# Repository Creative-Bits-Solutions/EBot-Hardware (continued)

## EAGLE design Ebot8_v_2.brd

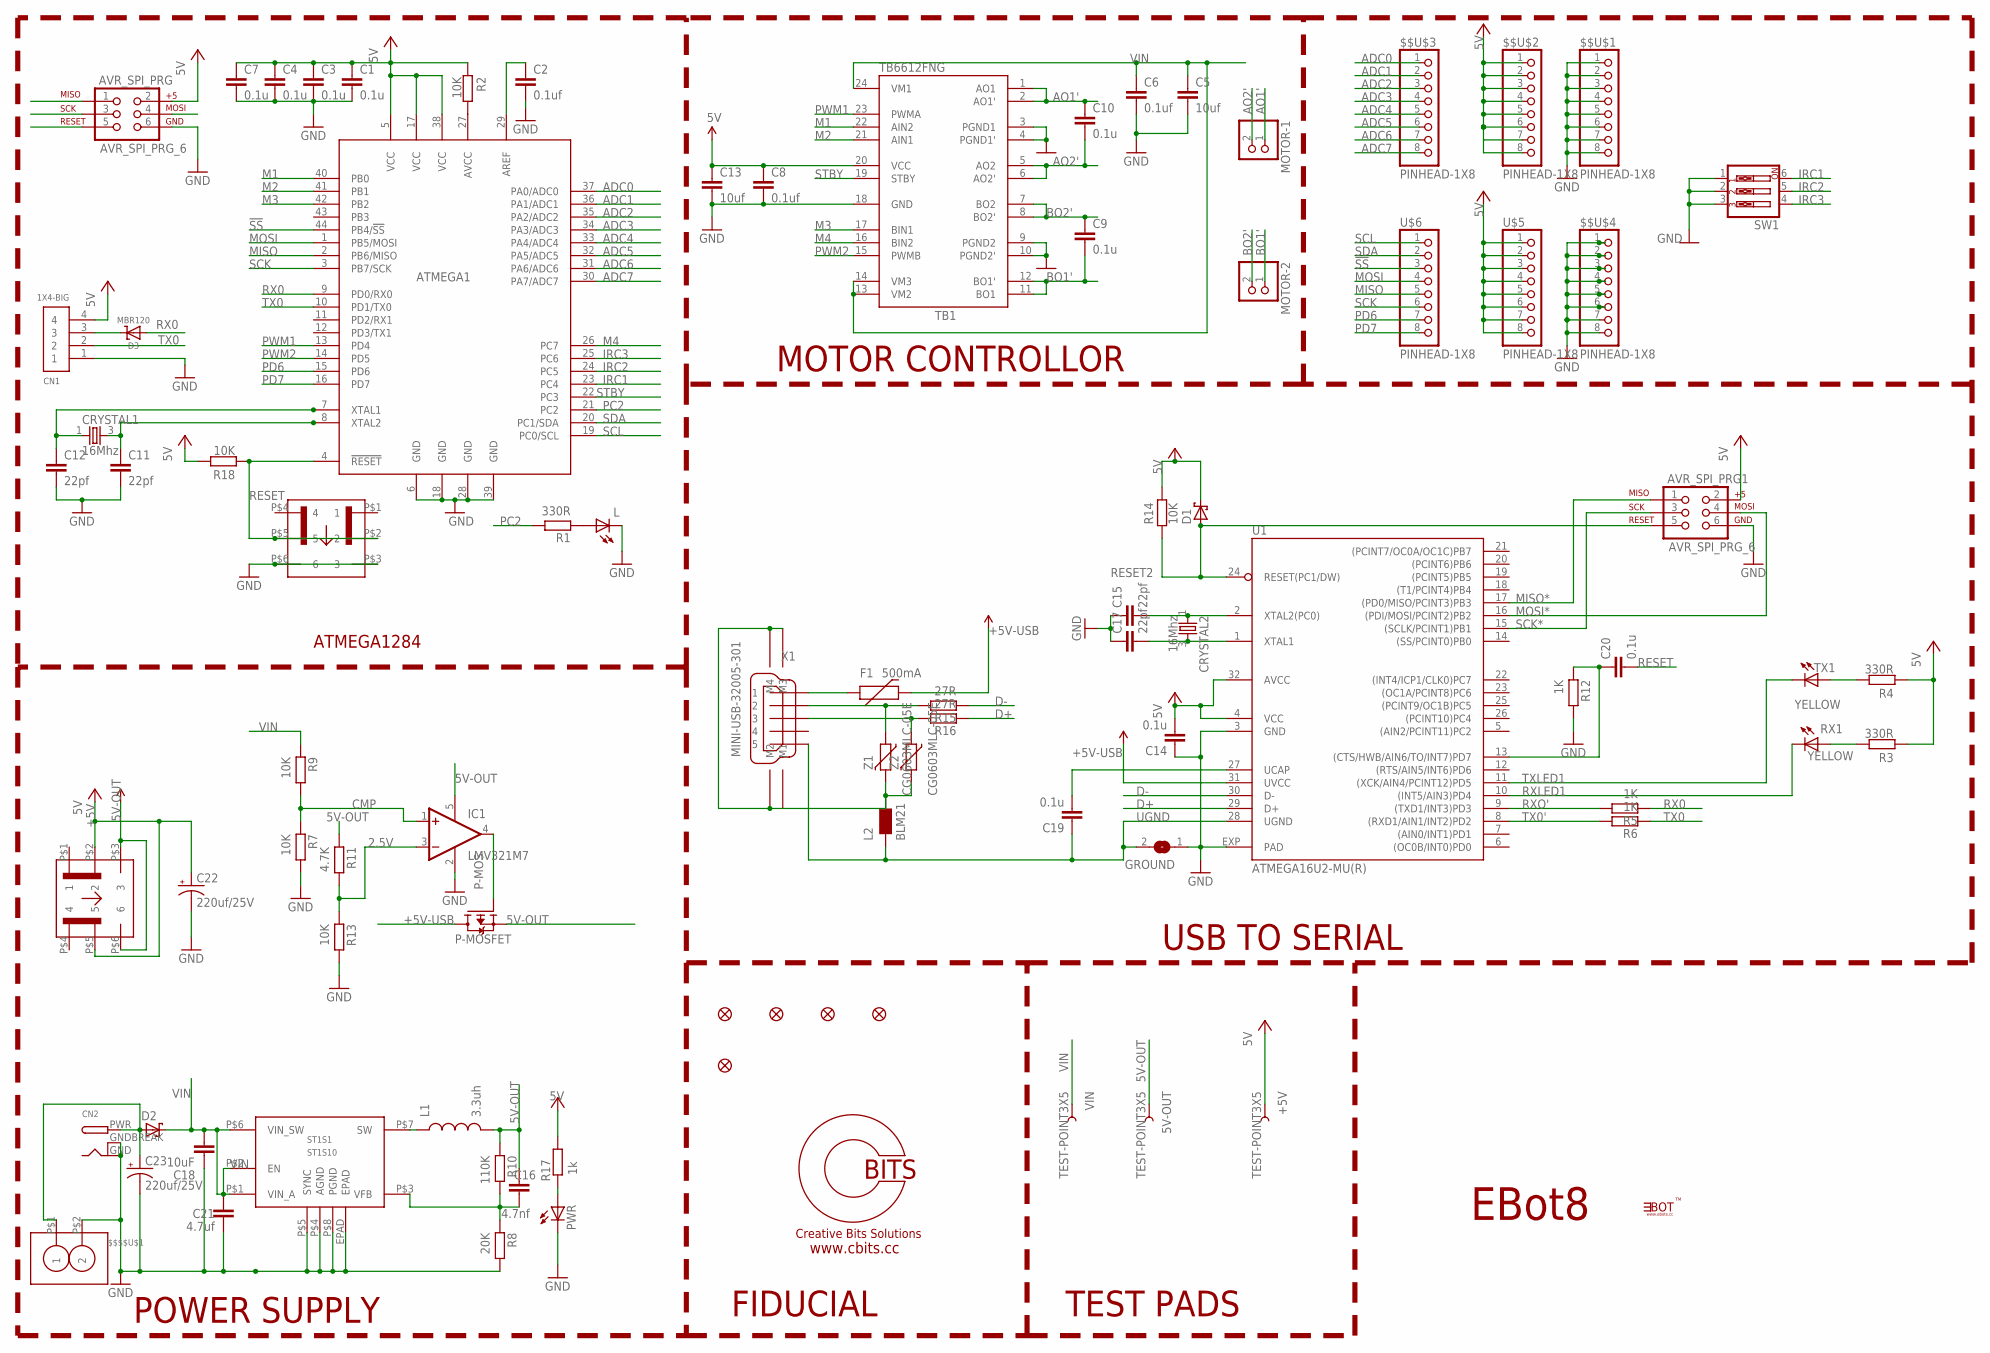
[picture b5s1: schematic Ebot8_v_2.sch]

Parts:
5V-OUT: TEST-POINT3X5; PAD.03X.05
$$$$U$1: SCREW_CONNECTOR-2PIN-; SCREW_CONNECTOR-2PIN-5.08MM
$$U$1, $$U$2, $$U$3, $$U$4: PINHEAD-1X8
+5V: TEST-POINT3X5; PAD.03X.05
ATMEGA1: ATMEGA164A/PA/324A/PA/644A/PA/1284/P; 44TQFP
AVR_SPI_PRG, AVR_SPI_PRG1: AVR_SPI_PRG_6; 2X3
C1, C3, C4, C7, C9, C10, C14, C19, C20: 0.1u; C0603
C2, C6, C8: 0.1uf; C0603
C5, C13: 10uf; C0603
C11, C12, C15, C17: 22pf; C0603
C16: 4.7nf; C0603
C18: 10uF; C0603
C21: 4.7uf; C0603
C22, C23: 220uf/25V; E2,5-6
CN1: 1X4-BIG; 1X04-BIG
CN2: DCBARRELPTH; DCJACK_2MM_PTH
CRYSTAL1, CRYSTAL2: 16Mhz; CRYSTAL-4PIN
D1, D2: SCHOTTKY-DIODESMA2; SCHOTTKY_SMA
D3: MBR120; SOD-123
F1: 500mA; PTC-1206
FID1, FID2, FID3, FID4, FID100: FIDUCIAL1.5X3; FIDUCIAL-1.5X3
GROUND: SJ
IC1: LMV321M7; SC70-5L
L: LEDCHIP-LED0603; CHIP-LED0603
L1: 3.3uh; CR54
L2: BLM21; 0805
LOGO1: CBITS_LOGO
MOTOR-1, MOTOR-2: PINHD-1X2; 1X02
P-MOS: P-MOSFET; SOT23-R
POWER: PUSHBUTTON_SWITCH-CW179-ND; PUSHBUTTON_SWITCH
PWR: LEDCHIP-LED0603; CHIP-LED0603
R1, R3, R4: 330R; R0603
R2, R7, R9, R13, R14, R18: 10K; R0603
R5, R6, R12: 1K; R0603
R8: 20K; R0603
R10: 110K; R0603
R11: 4.7K; R0603
R15, R16: 27R; R0603
R17: 1k; R0603
RESET: PUSHBUTTON_SWITCH-ON-MOM; PUSHBUTTON_SWITCH
RX1: YELLOW; CHIP-LED0603
ST1S1: ST1S10
SW1: SW_DIP-3; EDG-03
TB1: TB6612FNG; SSOP24
TX1: YELLOW; CHIP-LED0603
U1: ATMEGA16U2-MU(R); SMARTPRJ_ATMEL_QFN32
U$5, U$6: PINHEAD-1X8
U$14: EBOT_LOGO
VIN: TEST-POINT3X5; PAD.03X.05
X1: MINI-USB-32005-301; 32005-301
Z1, Z2: CG0603MLC-05E; CT/CN0603

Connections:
2.5V: IC1.3 (-IN), R11.2, R13.1
5V-OUT: 5V-OUT.P$1, C16.1, IC1.5 (V+), L1.P$2 (2), P-MOS.2 (S), POWER.P$3 (3), POWER.P$6 (6), R10.1, R11.1
!SS: ATMEGA1.44 (PB4/!SS), U$6.3
+5V: $$U$2.1, $$U$2.2, $$U$2.3, $$U$2.4, $$U$2.5, $$U$2.6, $$U$2.7, $$U$2.8, +5V.P$1, ATMEGA1.5 (VCC), ATMEGA1.17 (VCC), ATMEGA1.38 (VCC), AVR_SPI_PRG.2, AVR_SPI_PRG1.2, C1.1, C3.1, C4.1, C7.1, C8.1, C13.1, C14.2, C22.+, CN1.4, D1.C, POWER.P$2 (2), POWER.P$5 (5), R2.1, R3.1, R4.1, R14.2, R17.2, R18.2, TB1.20 (VCC), U1.4 (VCC), U1.32 (AVCC), U$5.1, U$5.2, U$5.3, U$5.4, U$5.5, U$5.6, U$5.7, U$5.8
+5V-USB: F1.2, P-MOS.3 (D), U1.31 (UVCC)
ADC0: $$U$3.1, ATMEGA1.37 (PA0/ADC0)
ADC1: $$U$3.2, ATMEGA1.36 (PA1/ADC1)
ADC2: $$U$3.3, ATMEGA1.35 (PA2/ADC2)
ADC3: $$U$3.4, ATMEGA1.34 (PA3/ADC3)
ADC4: $$U$3.5, ATMEGA1.33 (PA4/ADC4)
ADC5: $$U$3.6, ATMEGA1.32 (PA5/ADC5)
ADC6: $$U$3.7, ATMEGA1.31 (PA6/ADC6)
ADC7: $$U$3.8, ATMEGA1.30 (PA7/ADC7)
AO1': C10.1, MOTOR-1.1, TB1.1 (AO1), TB1.2 (AO1')
AO2': C10.2, MOTOR-1.2, TB1.5 (AO2), TB1.6 (AO2')
AREF: ATMEGA1.29 (AREF), C2.1
BO1': C9.2, MOTOR-2.1, TB1.11 (BO1), TB1.12 (BO1')
BO2': C9.1, MOTOR-2.2, TB1.7 (BO2), TB1.8 (BO2')
CMP: IC1.1 (+IN), R7.1, R9.2
D+: R16.1, U1.29 (D+)
D-: R15.1, U1.30 (D-)
GATE_CMD: IC1.4 (OUT), P-MOS.1 (G)
GND: $$$$U$1.P$2 (2), $$U$1.1, $$U$1.2, $$U$1.3, $$U$1.4, $$U$1.5, $$U$1.6, $$U$1.7, $$U$1.8, $$U$4.1, $$U$4.2, $$U$4.3, $$U$4.4, $$U$4.5, $$U$4.6, $$U$4.7, $$U$4.8, ATMEGA1.6 (GND), ATMEGA1.18 (GND), ATMEGA1.28 (GND), ATMEGA1.39 (GND), AVR_SPI_PRG.6, AVR_SPI_PRG1.6, C1.2, C2.2, C3.2, C4.2, C5.2, C6.2, C7.2, C8.2, C11.2, C12.2, C13.2, C14.1, C15.1, C17.1, C18.2, C21.2, C22.-, C23.-, CN1.1, CN2.GND, CN2.GNDBREAK, GROUND.1, IC1.2 (V-), L.C, PWR.C, R7.2, R8.2, R12.2, R13.2, RESET.P$3 (3), RESET.P$6 (6), ST1S1.EPAD, ST1S1.P$4 (AGND), ST1S1.P$5 (SYNC), ST1S1.P$8 (PGND), ST1S1.P$9 (GND), ST1S1.P$10 (GND), ST1S1.P$11 (GND), ST1S1.P$12 (GND), ST1S1.P$13 (GND), ST1S1.P$14 (GND), ST1S1.P$15 (GND), ST1S1.P$16 (GND), ST1S1.P$17 (GND), SW1.1, SW1.2, SW1.3, TB1.3 (PGND1), TB1.4 (PGND1'), TB1.9 (PGND2), TB1.10 (PGND2'), TB1.18 (GND), U1.3 (GND), U1.EXP (PAD)
IRC1: ATMEGA1.23 (PC4), SW1.6
IRC2: ATMEGA1.24 (PC5), SW1.5
IRC3: ATMEGA1.25 (PC6), SW1.4
M1: ATMEGA1.40 (PB0), TB1.22 (AIN2)
M2: ATMEGA1.41 (PB1), TB1.21 (AIN1)
M3: ATMEGA1.42 (PB2), TB1.17 (BIN1)
M4: ATMEGA1.26 (PC7), TB1.16 (BIN2)
MISO: ATMEGA1.2 (PB6/MISO), AVR_SPI_PRG.1, U$6.5
MISO*: AVR_SPI_PRG1.1, U1.17 ((PD0/MISO/PCINT3)PB3)
MOSI: ATMEGA1.1 (PB5/MOSI), AVR_SPI_PRG.4, U$6.4
MOSI*: AVR_SPI_PRG1.4, U1.16 ((PDI/MOSI/PCINT2)PB2)
unnamed: PWR.A, R17.1
unnamed: $$$$U$1.P$1 (1), C23.+, CN2.PWR, D2.A
unnamed: R3.2, RX1.A
unnamed: R4.2, TX1.A
unnamed: C15.2, CRYSTAL2.1, U1.2 (XTAL2(PC0))
unnamed: ATMEGA1.27 (AVCC), R2.2
unnamed: C17.2, CRYSTAL2.3 (2), U1.1 (XTAL1)
unnamed: C19.2, U1.27 (UCAP)
unnamed: C20.1, R12.1, U1.13 ((CTS/HWB/AIN6/TO/INT7)PD7)
unnamed: L2.2, X1.M1, X1.M2, X1.M3, X1.M4, Z1.2, Z2.2
unnamed: CN1.3, D3.C
unnamed: L.A, R1.1
unnamed: F1.1, X1.1
unnamed: R15.2, X1.2, Z1.1
unnamed: R16.2, X1.3, Z2.1
unnamed: L1.P$1 (1), ST1S1.P$7 (SW)
unnamed: C16.2, R8.1, R10.2, ST1S1.P$3 (VFB)
unnamed: ATMEGA1.8 (XTAL2), C11.1, CRYSTAL1.3 (2)
unnamed: ATMEGA1.7 (XTAL1), C12.1, CRYSTAL1.1
PC2: ATMEGA1.21 (PC2), R1.2
PD6: ATMEGA1.15 (PD6), U$6.7
PD7: ATMEGA1.16 (PD7), U$6.8
PWM1: ATMEGA1.13 (PD4), TB1.23 (PWMA)
PWM2: ATMEGA1.14 (PD5), TB1.15 (PWMB)
RESET: ATMEGA1.4 (!RESET), AVR_SPI_PRG.5, C20.2, R18.1, RESET.P$2 (2), RESET.P$5 (5)
RESET2: AVR_SPI_PRG1.5, D1.A, R14.1, U1.24 (RESET(PC1/DW))
RX0: ATMEGA1.9 (PD0/RX0), D3.A, R5.1
RXLED1: RX1.C, U1.10 ((INT5/AIN3)PD4)
RXO': R5.2, U1.9 ((TXD1/INT3)PD3)
SCK: ATMEGA1.3 (PB7/SCK), AVR_SPI_PRG.3, U$6.6
SCK*: AVR_SPI_PRG1.3, U1.15 ((SCLK/PCINT1)PB1)
SCL: ATMEGA1.19 (PC0/SCL), U$6.1
SDA: ATMEGA1.20 (PC1/SDA), U$6.2
STBY: ATMEGA1.22 (PC3), TB1.19 (STBY)
TX0: ATMEGA1.10 (PD1/TX0), CN1.2, R6.1
TX0': R6.2, U1.8 ((RXD1/AIN1/INT2)PD2)
TXLED1: TX1.C, U1.11 ((XCK/AIN4/PCINT12)PD5)
UGND: C19.1, GROUND.2, L2.1, U1.28 (UGND), X1.5
VIN: C5.1, C6.1, C18.1, C21.1, D2.C, R9.1, ST1S1.P$1 (VIN_A), ST1S1.P$2 (EN), ST1S1.P$6 (VIN_SW), TB1.13 (VM2), TB1.14 (VM3), TB1.24 (VM1), VIN.P$1

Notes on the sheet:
ATMEGA1284
MOTOR CONTROLLOR
USB TO SERIAL
POWER SUPPLY
FIDUCIAL
TEST PADS
EBot8

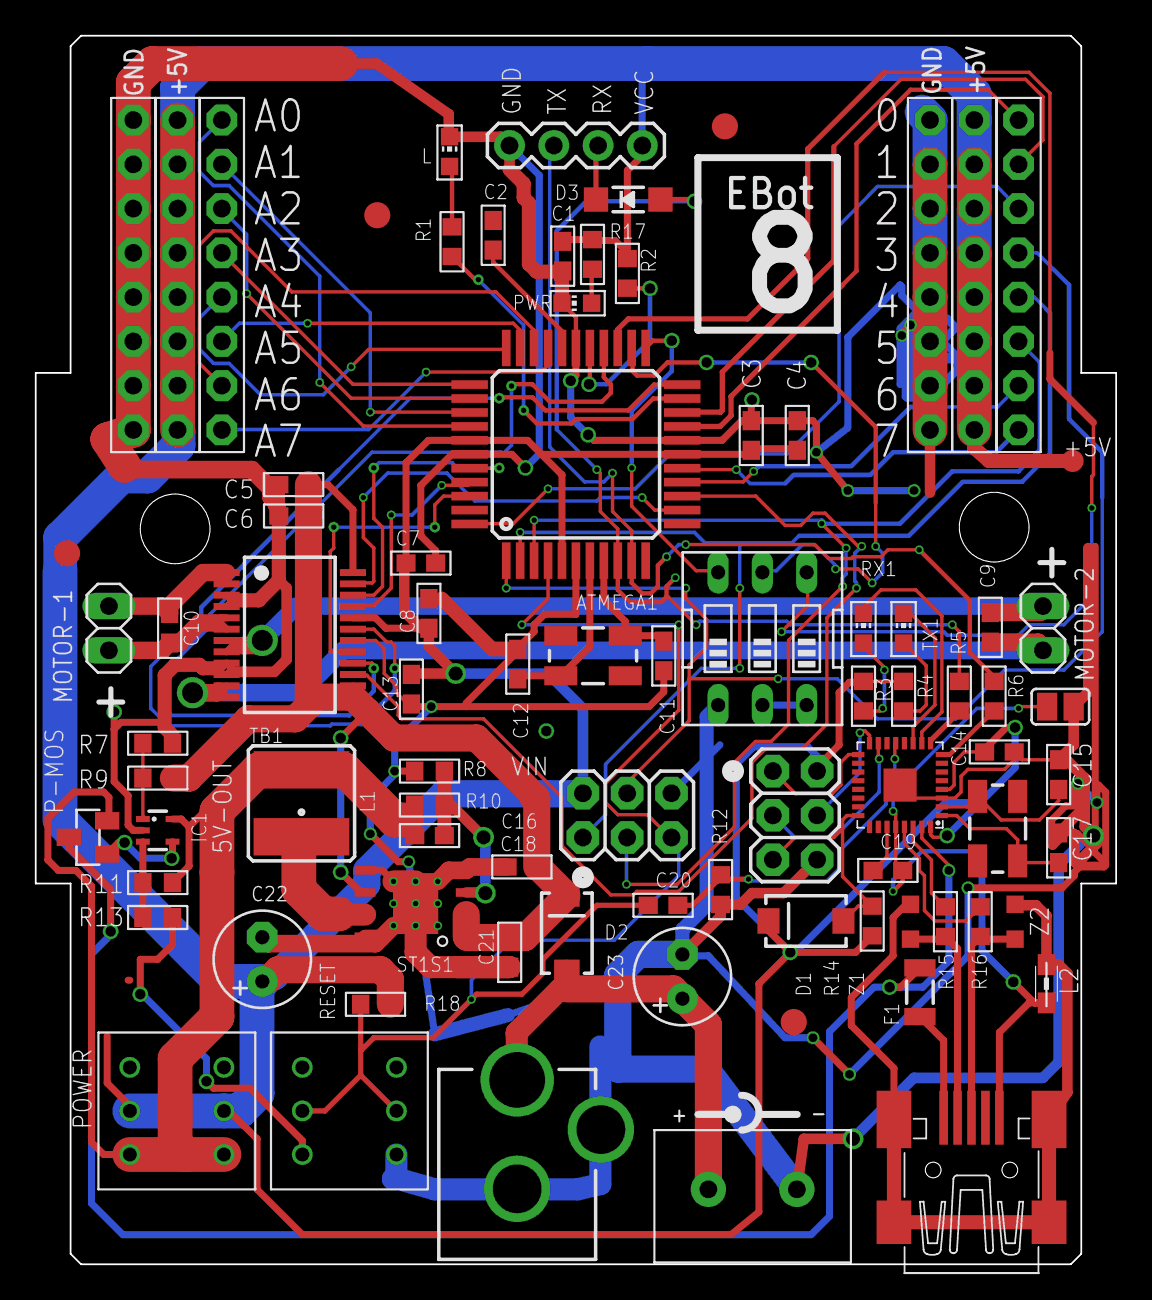
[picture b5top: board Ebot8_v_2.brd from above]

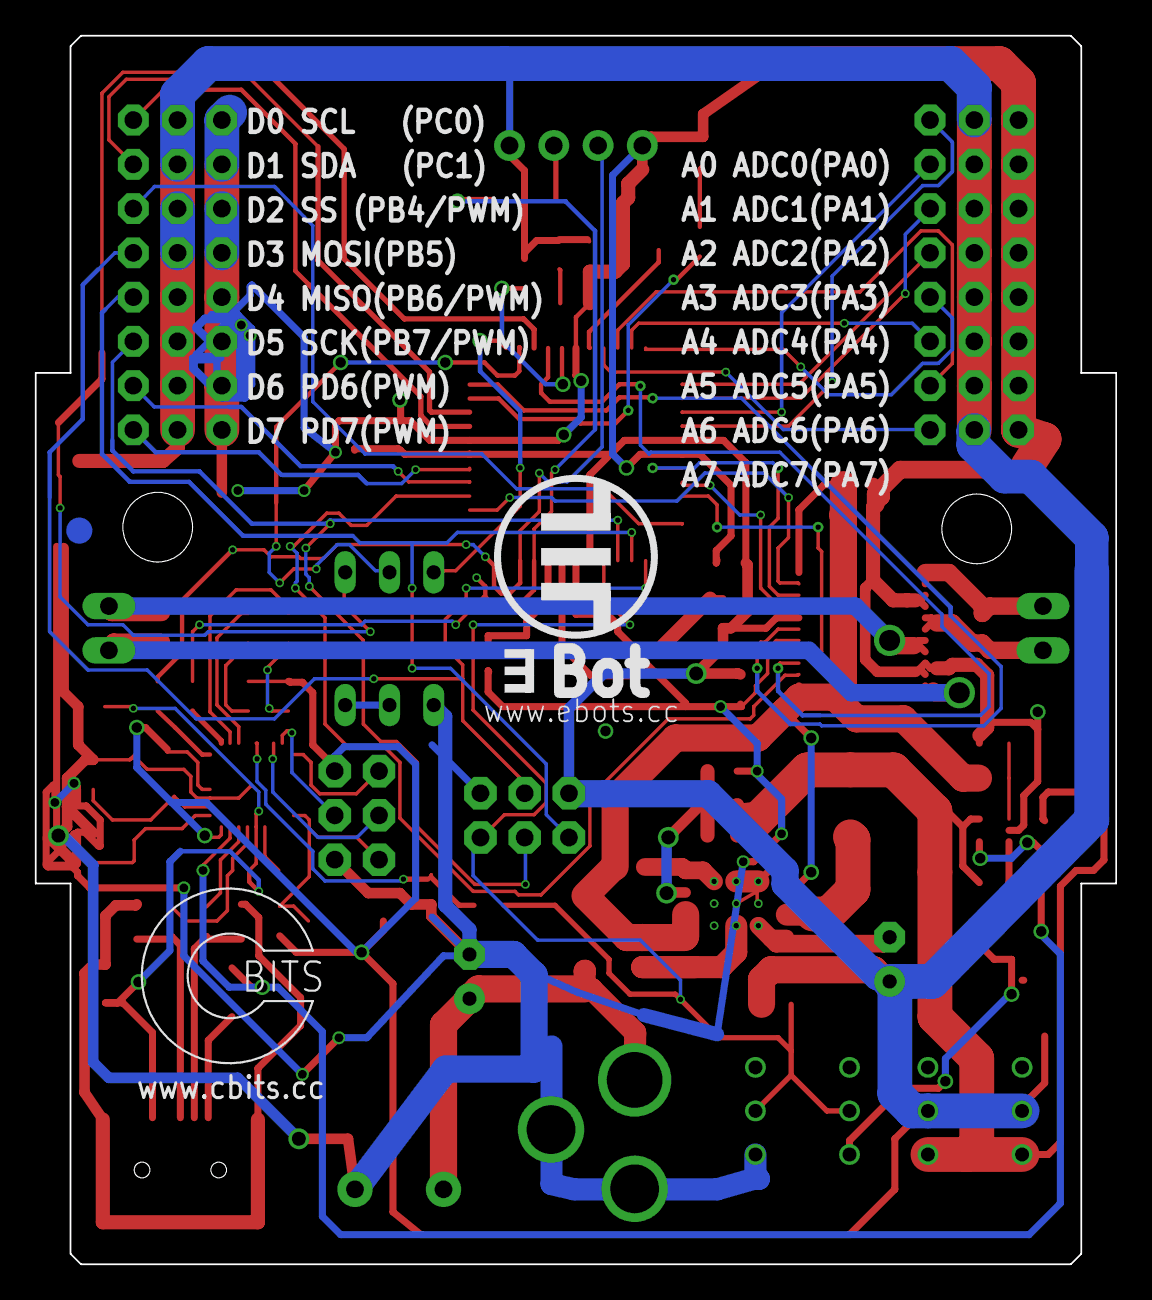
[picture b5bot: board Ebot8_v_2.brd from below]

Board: 2 copper layers, 62.0 x 70.5 mm, 89 parts (3 on the bottom side), 73 nets.

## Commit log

2018-04-12 Initial Commit to GitHub
    Initial Commit to GitHub
2018-04-12 EBot-8 design
2018-04-12 EBot sensors
2018-04-12 EBot Sunny
2018-04-12 EBot-4
